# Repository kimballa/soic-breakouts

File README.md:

SOIC Breakouts
==============

Breakout boards for {8, 14, 16}-pin SOIC and TSSOP ICs
that fit in a standard DIP width on a breadboard.

The IC itself sits to the side of the pin headers rather than between them, to achieve a
narrow breakout board profile (10.3mm) that does not straddle an extra row of pins on one
or the other side of the breadboard centerline. 

A separate through-hole exists in each SOIC board, connected to the ground plane. Solder a
resistor leg or other thin wire from the `GND` hole to top of the header pin that
represents ground for the IC. (Or leave floating if there is no appropriate ground pin for
the IC.)

## Gerber files

The latest gerber files for submitting to a board fab are in the `rtm/` directory.

If submitting to JLCPCB, select 'panel by customer', 'number of designs' = 3. 

## Panelization

The main project file includes one of each representative breakout board. Panels with 8 of
each SOIC or 8 of each TSSOP format were generated using KiKit. If you change the main PCB
CAD file, you should then open a KiCad Command Prompt in this directory and run `python
panelize.py`. You can edit `panelize.py` first to set variables related to the output file
to generate. You need to edit the script to select B1-B3 (SOIC), or B4-B6 (TSSOP boards)
for panelization.

### Script notes:

The current layout (n=8) is intended to fit in the 100x100 mm area that offers the best
deal for JLCPCB, but you can extend wider. The script would need to be modified to include
more than one row of each board. The script also assumes that all boards are the same
width, and may misalign columns if not accounted-for in any future modification that
changes some of the board widths.

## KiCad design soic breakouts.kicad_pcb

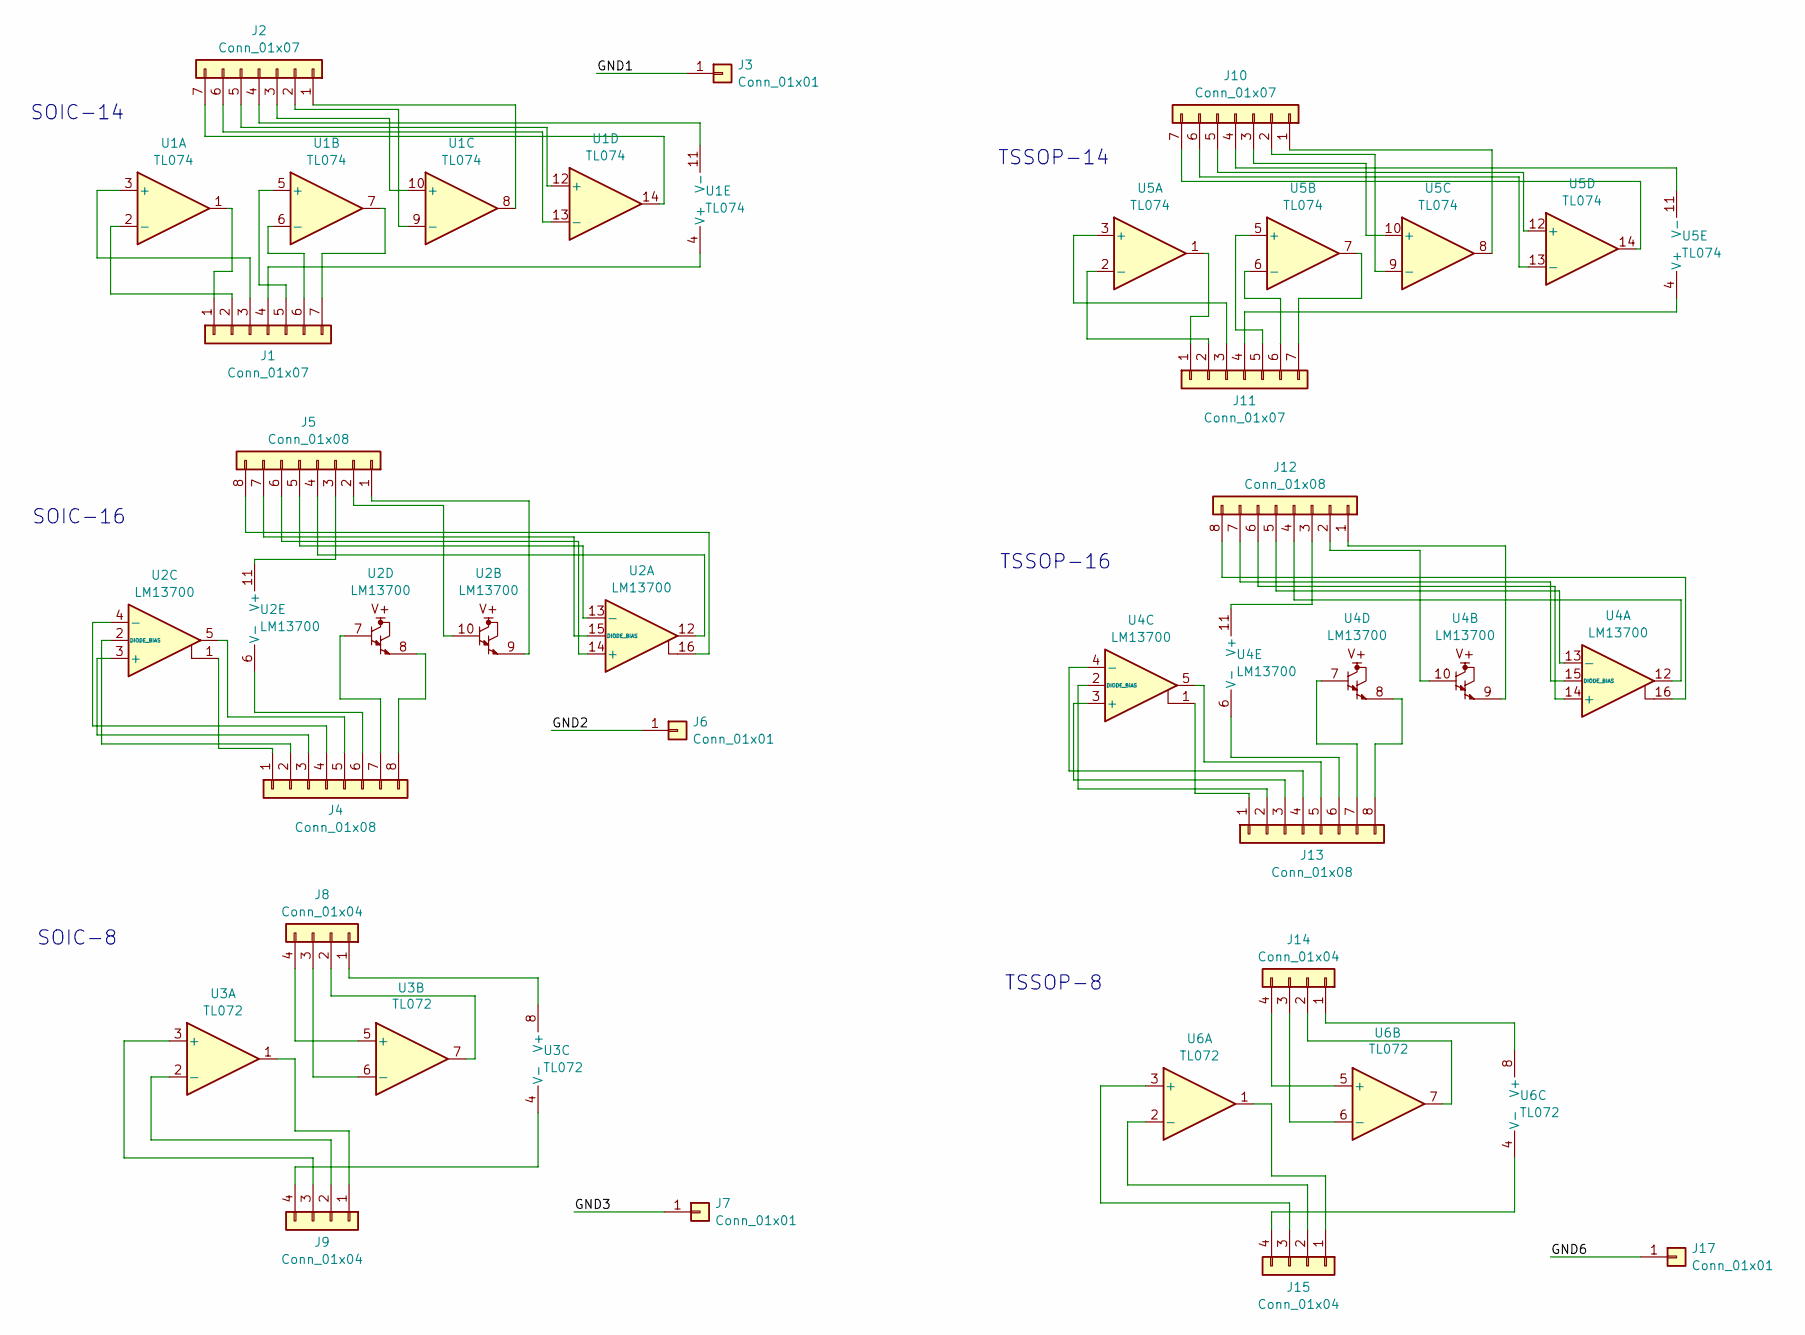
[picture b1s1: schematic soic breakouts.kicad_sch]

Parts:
J1, J2, J10, J11: Conn_01x07; PinHeader_1x07_P2.54mm_Vertical
J3, J6, J7, J17: Conn_01x01; TP_HeaderPin_P2.54mm_round
J4, J5, J12, J13: Conn_01x08; PinHeader_1x08_P2.54mm_Vertical
J8, J9, J14, J15: Conn_01x04; PinHeader_1x04_P2.54mm_Vertical
U1: TL074; TI_SOIC_D_R-PDSO-G14
U2: LM13700; TI_SOIC_D_R-PDSO-16
U3: TL072; TI_SOIC_D_R-PDSO-8
U4: LM13700; TSSOP-16_4.4x5mm_P0.65mm
U5: TL074; TI_TSSOP_PW0014A
U6: TL072; TI_TSSOP_PW0008A

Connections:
/GND1: J3.1
/GND2: J6.1
/GND3: J7.1
/GND6: J17.1
unnamed: J1.1, U1.1
unnamed: J1.2, U1.2 (-)
unnamed: J1.3, U1.3 (+)
unnamed: J1.4, U1.4 (V+)
unnamed: J1.5, U1.5 (+)
unnamed: J1.6, U1.6 (-)
unnamed: J1.7, U1.7
unnamed: J2.1, U1.8
unnamed: J2.2, U1.9 (-)
unnamed: J2.3, U1.10 (+)
unnamed: J2.4, U1.11 (V-)
unnamed: J2.5, U1.12 (+)
unnamed: J2.6, U1.13 (-)
unnamed: J2.7, U1.14
unnamed: J4.1, U2.1
unnamed: J4.2, U2.2 (DIODE_BIAS)
unnamed: J4.3, U2.3 (+)
unnamed: J4.4, U2.4 (-)
unnamed: J4.5, U2.5
unnamed: J4.6, U2.6 (V-)
unnamed: J4.7, U2.7
unnamed: J4.8, U2.8
unnamed: J5.1, U2.9
unnamed: J5.2, U2.10
unnamed: J5.3, U2.11 (V+)
unnamed: J5.4, U2.12
unnamed: J5.5, U2.13 (-)
unnamed: J5.6, U2.14 (+)
unnamed: J5.7, U2.15 (DIODE_BIAS)
unnamed: J5.8, U2.16
unnamed: J8.1, U3.8 (V+)
unnamed: J8.2, U3.7
unnamed: J8.3, U3.6 (-)
unnamed: J8.4, U3.5 (+)
unnamed: J9.1, U3.1
unnamed: J9.2, U3.2 (-)
unnamed: J9.3, U3.3 (+)
unnamed: J9.4, U3.4 (V-)
unnamed: J10.1, U5.8
unnamed: J10.2, U5.9 (-)
unnamed: J10.3, U5.10 (+)
unnamed: J10.4, U5.11 (V-)
unnamed: J10.5, U5.12 (+)
unnamed: J10.6, U5.13 (-)
unnamed: J10.7, U5.14
unnamed: J11.1, U5.1
unnamed: J11.2, U5.2 (-)
unnamed: J11.3, U5.3 (+)
unnamed: J11.4, U5.4 (V+)
unnamed: J11.5, U5.5 (+)
unnamed: J11.6, U5.6 (-)
unnamed: J11.7, U5.7
unnamed: J12.1, U4.9
unnamed: J12.2, U4.10
unnamed: J12.3, U4.11 (V+)
unnamed: J12.4, U4.12
unnamed: J12.5, U4.13 (-)
unnamed: J12.6, U4.14 (+)
unnamed: J12.7, U4.15 (DIODE_BIAS)
unnamed: J12.8, U4.16
unnamed: J13.1, U4.1
unnamed: J13.2, U4.2 (DIODE_BIAS)
unnamed: J13.3, U4.3 (+)
unnamed: J13.4, U4.4 (-)
unnamed: J13.5, U4.5
unnamed: J13.6, U4.6 (V-)
unnamed: J13.7, U4.7
unnamed: J13.8, U4.8
unnamed: J14.1, U6.8 (V+)
unnamed: J14.2, U6.7
unnamed: J14.3, U6.6 (-)
unnamed: J14.4, U6.5 (+)
unnamed: J15.1, U6.1
unnamed: J15.2, U6.2 (-)
unnamed: J15.3, U6.3 (+)
unnamed: J15.4, U6.4 (V-)

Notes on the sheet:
SOIC-14
TSSOP-8
SOIC-8
TSSOP-14
SOIC-16
TSSOP-16

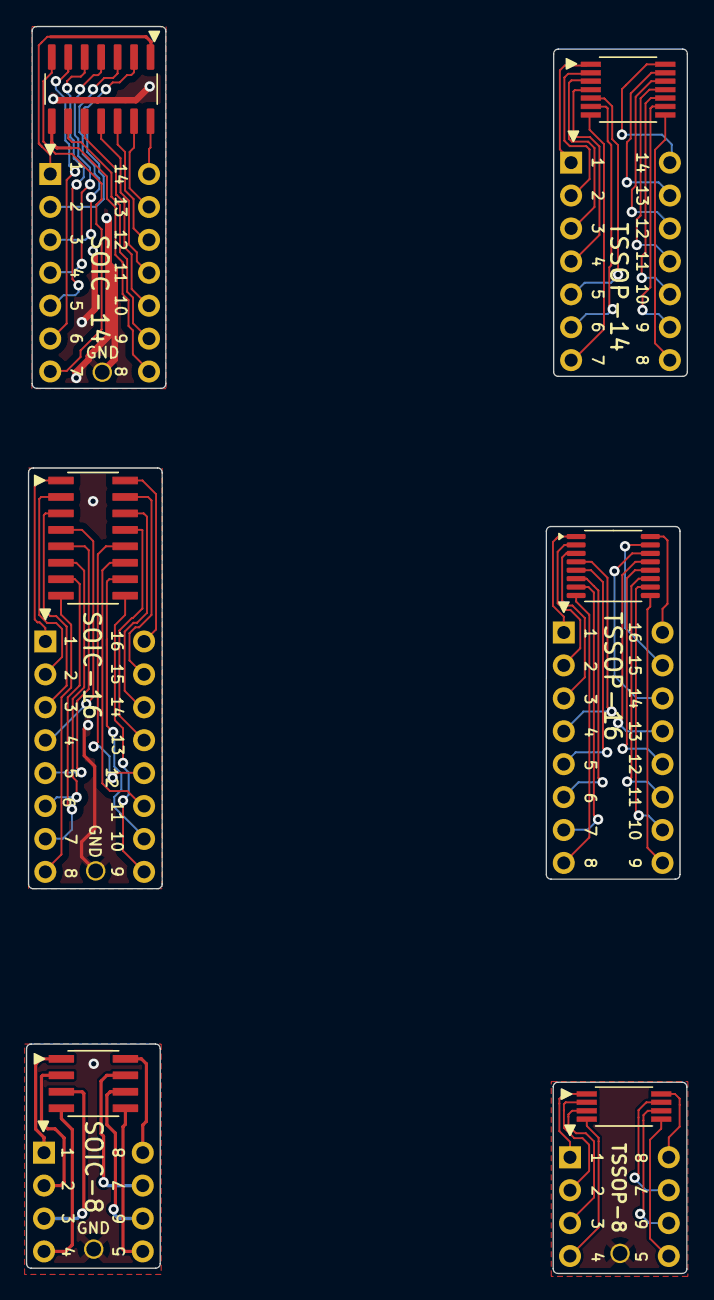
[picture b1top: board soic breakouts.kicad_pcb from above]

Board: 2 copper layers, 51.0 x 96.2 mm, 28 parts (0 on the bottom side), 76 nets.

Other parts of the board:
B1, B2, B3, B4, B5, B6: Board

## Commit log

2023-12-29 Add gitignore file.
2023-12-29 Add readme.
2023-12-29 Add project files.
2023-12-29 Some schema edits.
2023-12-29 Add v1.0 RTM gerbers.
2024-12-01 Add SOIC-8.
    * Update to KiCAD 8 format.
    * Add SOIC-8 footprint breakout.
    * Update to new IPC pin 1 (triangle/arrow) indicator throughout.
    * Make pin 1 on header more obvious with IPC indicator throughout.
    * Increase silkscreen font size for main label per breakout board.
2024-12-01 Add TSSOP-8, -14, -16 breakouts.
    Now have SOIC and TSSOP for 8/14/16 pin variants.
2024-12-02 Add KiKit panelization script.
    Added python script using KiKit SDK to generate separate
    SOIC and TSSOP breakout board panels.
2024-12-02 Add v2.0 RTM gerbers for SOIC and TSSOP panels.
2024-12-02 Update README.
